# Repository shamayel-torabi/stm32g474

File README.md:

# stm32g474
stm32g474 development board

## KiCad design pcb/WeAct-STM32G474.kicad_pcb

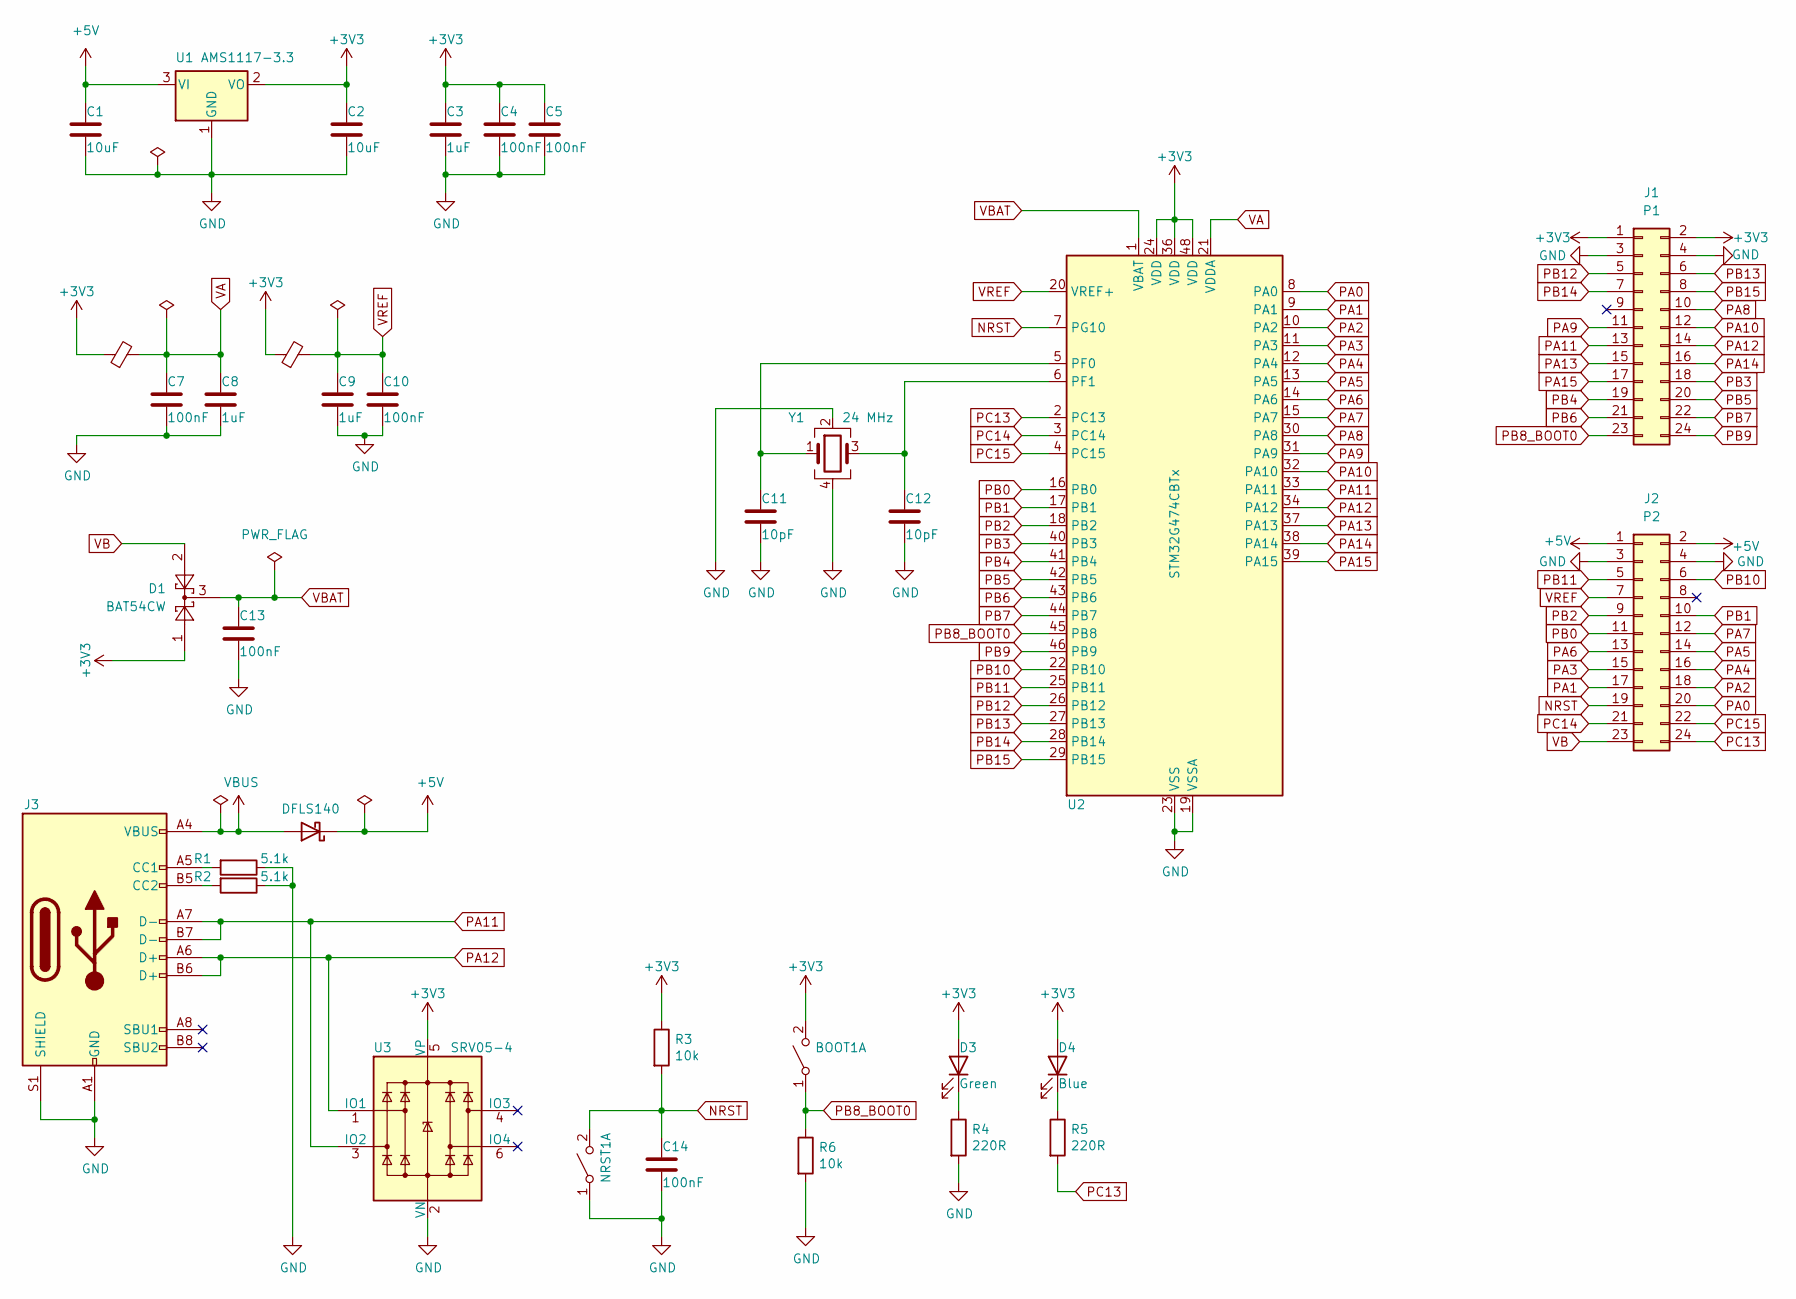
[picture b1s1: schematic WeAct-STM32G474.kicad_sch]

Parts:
BOOT1: SW_DPST_x2; SW_Push_1P1T_NO_E-Switch_TL3301NxxxxxG
C1, C2: C_10UF_0805; C_0805_2012Metric; LCSC C15850
C3: C_1UF_0805; C_0603_1608Metric; LCSC C15849
C4, C5, C7, C10, C13, C14: C_100NF_0603; C_0603_1608Metric; LCSC C14663
C8, C9: C_1UF_0603; C_0603_1608Metric; LCSC C15849
C11, C12: C_10PF_0603; C_0603_1608Metric; LCSC C1648
D1: BAT54CW; TSOT-23
D2: DFLS140; D_PowerDI-123; LCSC C8598
D3: LED_GREEN_0603; LED_0603_1608Metric; LCSC C72043
D4: LED_BLUE_0603; LED_0603_1608Metric; LCSC C72041
FB1, FB2: FB_0805; L_0805_2012Metric; LCSC C1002
J1: P1; PinHeader_2x12_P2.54mm_Vertical
J2: P2; PinHeader_2x12_P2.54mm_Vertical
J3: USB_C_Receptacle_G-Switch_GT-USB-7010ASV; LCSC C165948
NRST1: SW_DPST_x2; SW_Push_1P1T_NO_E-Switch_TL3301NxxxxxG
R1, R2: R_5.1K_0603; R_0603_1608Metric; LCSC C23186
R3, R6: R_10K_0603; R_0603_1608Metric; LCSC C25804
R4, R5: R_220_0603; R_0603_1608Metric; LCSC C22962
U1: AMS1117-3.3; SOT-223-3_TabPin2; LCSC C6186
U2: STM32G474CBTx; LQFP-48_7x7mm_P0.5mm
U3: SRV05-4; SOT-23-6; LCSC C85364
Y1: X_24MHZ; Crystal_SMD_2016-4Pin_2.0x1.6mm; LCSC C13738

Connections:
+3V3: BOOT1.2 (B), C2.1, C3.1, C4.1, C5.1, D1.1, D3.2 (A), D4.2 (A), FB1.1, FB2.1, J1.1, J1.2, R3.1, U1.2 (VO), U2.24 (VDD), U2.36 (VDD), U2.48 (VDD), U3.5 (VP); also elsewhere on the board
+5V: C1.1, D2.1 (K), J2.1, J2.2, U1.3 (VI)
GND: C1.2, C2.2, C3.2, C4.2, C5.2, C7.2, C8.2, C9.2, C10.2, C11.2, C12.2, C13.2, C14.2, J1.3, J1.4, J2.3, J2.4, J3.A1 (GND), J3.A12 (GND), J3.B1 (GND), J3.B12 (GND), J3.S1 (SHIELD), NRST1.1 (A), R1.1, R2.1, R4.2, R6.2, U1.1 (GND), U2.19 (VSSA), U2.23 (VSS), U2.35 (VSS), U2.47 (VSS), U3.2 (VN), Y1.2, Y1.4
NRST: C14.1, J2.19, NRST1.2 (B), R3.2, U2.7 (PG10)
unnamed: D3.1 (K), R4.1
unnamed: D4.1 (K), R5.1
unnamed: J3.A5 (CC1), R1.2
unnamed: J3.B5 (CC2), R2.2
unnamed: C11.1, U2.5 (PF0), Y1.1
unnamed: C12.1, U2.6 (PF1), Y1.3
PA0: J2.20, U2.8 (PA0)
PA1: J2.17, U2.9 (PA1)
PA2: J2.18, U2.10 (PA2)
PA3: J2.15, U2.11 (PA3)
PA4: J2.16, U2.12 (PA4)
PA5: J2.14, U2.13 (PA5)
PA6: J2.13, U2.14 (PA6)
PA7: J2.12, U2.15 (PA7)
PA8: J1.10, U2.30 (PA8)
PA9: J1.11, U2.31 (PA9)
PA10: J1.12, U2.32 (PA10)
PA11: J1.13, J3.A7 (D-), J3.B7 (D-), U2.33 (PA11), U3.3 (IO2)
PA12: J1.14, J3.A6 (D+), J3.B6 (D+), U2.34 (PA12), U3.1 (IO1)
PA13: J1.15, U2.37 (PA13)
PA14: J1.16, U2.38 (PA14)
PA15: J1.17, U2.39 (PA15)
PB0: J2.11, U2.16 (PB0)
PB1: J2.10, U2.17 (PB1)
PB2: J2.9, U2.18 (PB2)
PB3: J1.18, U2.40 (PB3)
PB4: J1.19, U2.41 (PB4)
PB5: J1.20, U2.42 (PB5)
PB6: J1.21, U2.43 (PB6)
PB7: J1.22, U2.44 (PB7)
PB8_BOOT0: BOOT1.1 (A), J1.23, R6.1, U2.45 (PB8); also elsewhere on the board
PB9: J1.24, U2.46 (PB9)
PB10: J2.6, U2.22 (PB10)
PB11: J2.5, U2.25 (PB11)
PB12: J1.5, U2.26 (PB12)
PB13: J1.6, U2.27 (PB13)
PB14: J1.7, U2.28 (PB14)
PB15: J1.8, U2.29 (PB15)
PC13: J2.24, R5.2, U2.2 (PC13)
PC14: J2.21, U2.3 (PC14)
PC15: J2.22, U2.4 (PC15)
VA: C7.1, C8.1, FB1.2, U2.21 (VDDA)
VB: D1.2, J2.23
VBAT: C13.1, D1.3, U2.1 (VBAT)
VBUS: D2.2 (A), J3.A4 (VBUS), J3.A9 (VBUS), J3.B4 (VBUS), J3.B9 (VBUS)
VREF: C9.1, C10.1, FB2.2, J2.7, U2.20 (VREF+)

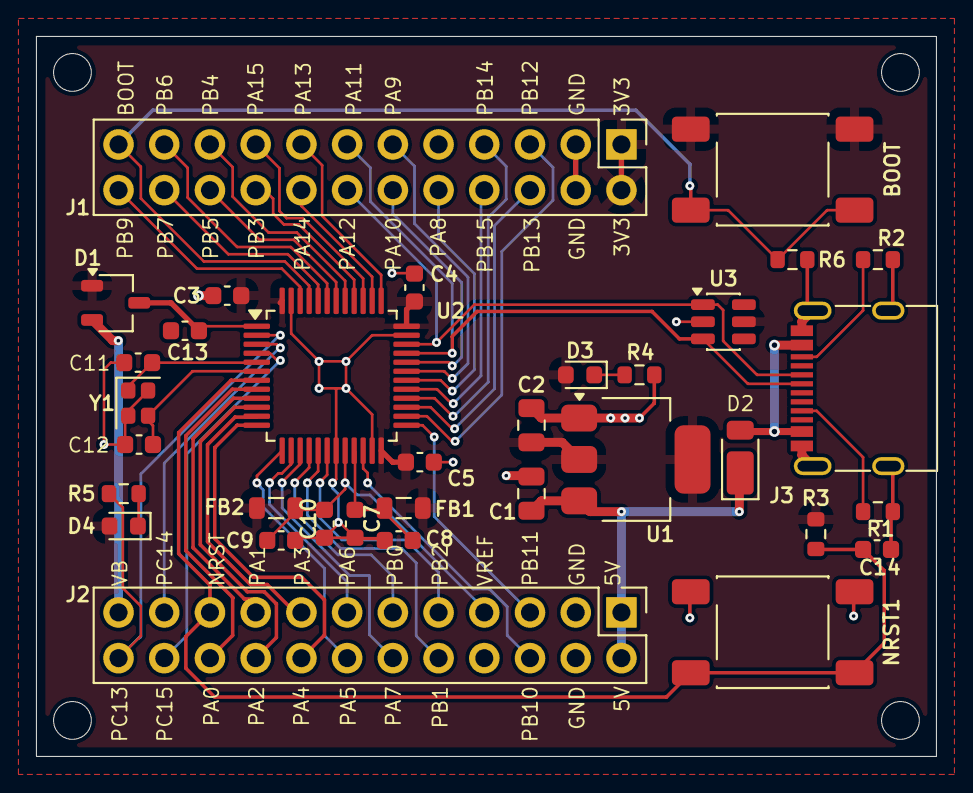
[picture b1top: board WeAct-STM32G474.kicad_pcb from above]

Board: 2 copper layers, 50.0 x 40.0 mm, 34 parts (0 on the bottom side), 50 nets.

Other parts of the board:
BOOT: SW_DPST_x2; SW_Push_1P1T_NO_E-Switch_TL3301NxxxxxG

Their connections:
+3V3: BOOT.2 (B); also elsewhere on the board
PB8_BOOT0: BOOT.1 (A); also elsewhere on the board

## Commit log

2025-10-14 initialize
2025-10-18 Complete PCB
2025-10-19 pcb design phase 1
2025-10-19 pcb design phase 2
2025-10-19 pcb design phase 3
2025-10-19 pcb design phase 4
2025-10-20 pcb design complete
2025-10-21 pcb design update 1
2025-10-21 pcb design update 2
2025-11-15 fix usb type-c placement
2025-11-30 update new
